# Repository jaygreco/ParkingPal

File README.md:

# ParkingPal
An open-source distance meter for easy garage parking. See [the thingiverse page](https://www.thingiverse.com/thing:3448336) for more info.

## How to use
Compile for the Arduino Pro Micro and upload. By default, the firmware is built for 8 LEDs (the NeoPixel Stick), and will poll the sensor at 3Hz until the read distance has been stable for roughly 10 seconds.

Single-pressing the button will change the operating mode. Double-clicking will cycle the brightness, and long-pressing will set the default parking distance. To set the default parking distance properly, park the car at the normal parking distance, and then long-press the button while making sure to stay clear of the ultrasonic sensor. Once set, the buzzer will beep once.

There are some configuration options in `config.h`. They should be pretty self-explanatory. There really isn't much need to change these unless you want to tweak some specific behavior. 

## Parts list
There's a more detailed BOM [here](https://github.com/jaygreco/ParkingPal/blob/master/PCB/0.1/MCU/MCU_BOM.xlsx).
### Required
| Qty | Part              | Link                                                                |
|-----|-------------------|---------------------------------------------------------------------|
| 1   | Arduino Pro Micro | [SparkFun](https://www.sparkfun.com/products/12640)                 |
| 1   | NeoPixel Stick    | [SparkFun](https://www.sparkfun.com/products/12661)                 |
| 1   | HC-SR04 Sensor    | [SparkFun](https://www.sparkfun.com/products/13959)                 |
| 1   | SMT Pushbutton    | [SparkFun](https://www.sparkfun.com/products/8720)                  |
| 1   | USB A Connector   | [Digikey](https://www.digikey.com/products/en?keywords=380-1412-ND) |
| 1   | PCB - MCU         | [OSHPark](https://oshpark.com/shared_projects/L5AVMKPm)             |
| 1   | PCB - SMU         | [OSHPark](https://oshpark.com/shared_projects/UerOD9Ji)             |

### Optional (to include buzzer)
| Qty | Part            | Link                                                                        |
|-----|-----------------|-----------------------------------------------------------------------------|
| 1   | 12mm Buzzer     | [SparkFun](https://www.sparkfun.com/products/7950)                          |
| 1   | 10k Resistor    | [Digikey](https://www.digikey.com/products/en?keywords=RMCF0201FT10K0CT-ND) |
| 1   | 2N7002 N-Ch Fet | [Digikey](https://www.digikey.com/products/en?keywords=2N7002-TPMSCT-ND)    |

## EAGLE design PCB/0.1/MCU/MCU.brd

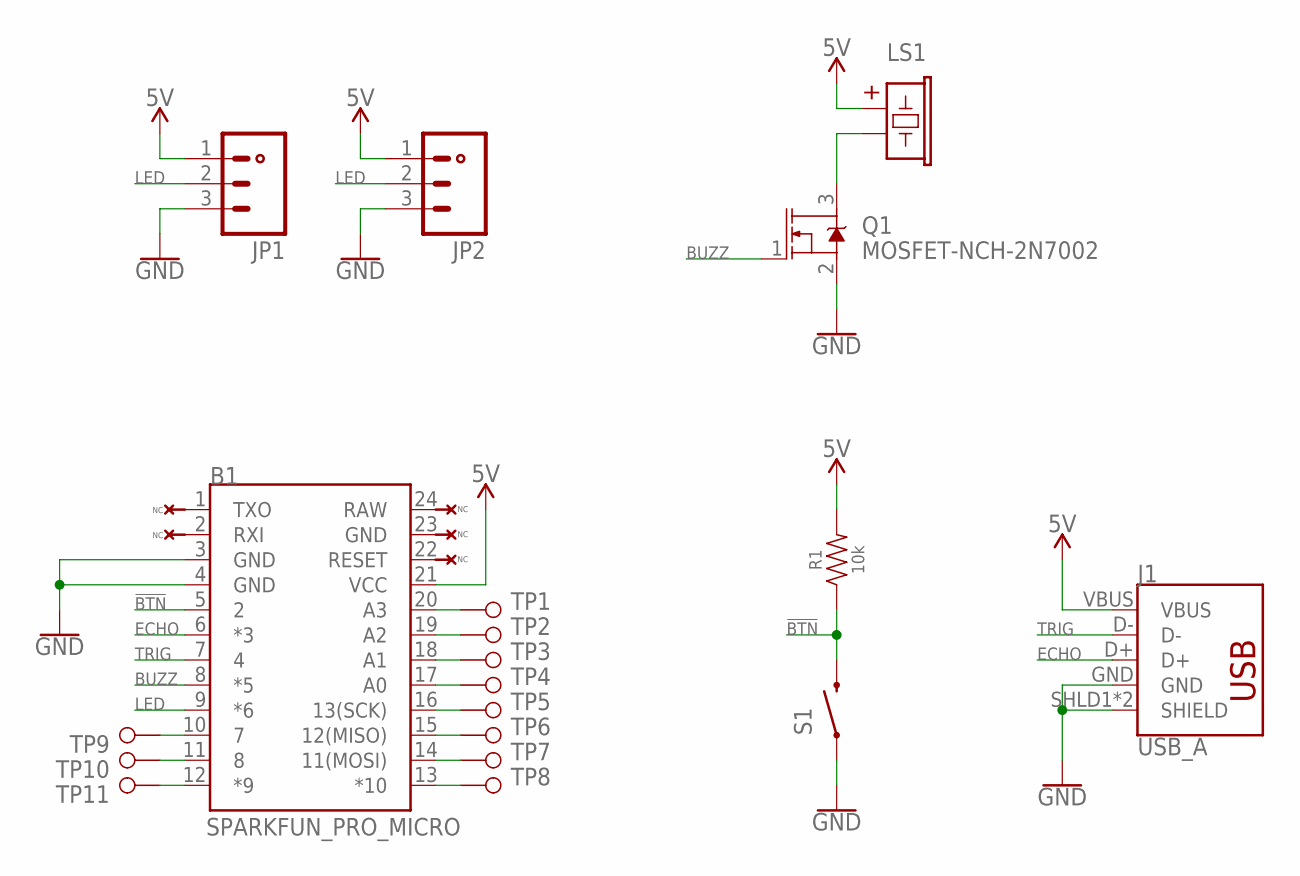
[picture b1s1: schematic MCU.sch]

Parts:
B1: SPARKFUN_PRO_MICRO
J1: USB_A; USB-A-H
JP1, JP2: M03PTH; 1X03
LS1: BUZZER-PTH_KIT; BUZZER-12MM-KIT
Q1: MOSFET-NCH-2N7002; SOT23-3
R1: 10k; 0603
S1: SWITCH-MOMENTARY-2SMD-REDUNDANT; TACTILE-SWITCH-SMD
TP1, TP2, TP3, TP4, TP5, TP6, TP7, TP8, TP9, TP10, TP11: TEST-POINT3X5; PAD.03X.05

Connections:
5V: B1.21 (VCC), J1.VBUS, JP1.1, JP2.1, LS1.+ (1), R1.2
!BTN: B1.5 (2), R1.1, S1.3 (2), S1.4 (2)
BUZZ: B1.8 (*5), Q1.1 (G)
ECHO: B1.6 (*3), J1.D+
GND: B1.3 (GND), B1.4 (GND), B1.23 (GND), J1.GND, J1.SHLD1 (SHIELD), J1.SHLD2 (SHIELD), JP1.3, JP2.3, Q1.2 (S), S1.1, S1.2 (1)
LED: B1.9 (*6), JP1.2, JP2.2
unnamed: B1.16 (13(SCK)), TP5.P$1
unnamed: B1.15 (12(MISO)), TP6.P$1
unnamed: B1.14 (11(MOSI)), TP7.P$1
unnamed: LS1.- (2), Q1.3 (D)
unnamed: B1.13 (*10), TP8.P$1
unnamed: B1.20 (A3), TP1.P$1
unnamed: B1.19 (A2), TP2.P$1
unnamed: B1.18 (A1), TP3.P$1
unnamed: B1.17 (A0), TP4.P$1
unnamed: B1.10 (7), TP9.P$1
unnamed: B1.11 (8), TP10.P$1
unnamed: B1.12 (*9), TP11.P$1
RAW: B1.24 (RAW)
TRIG: B1.7 (4), J1.D-

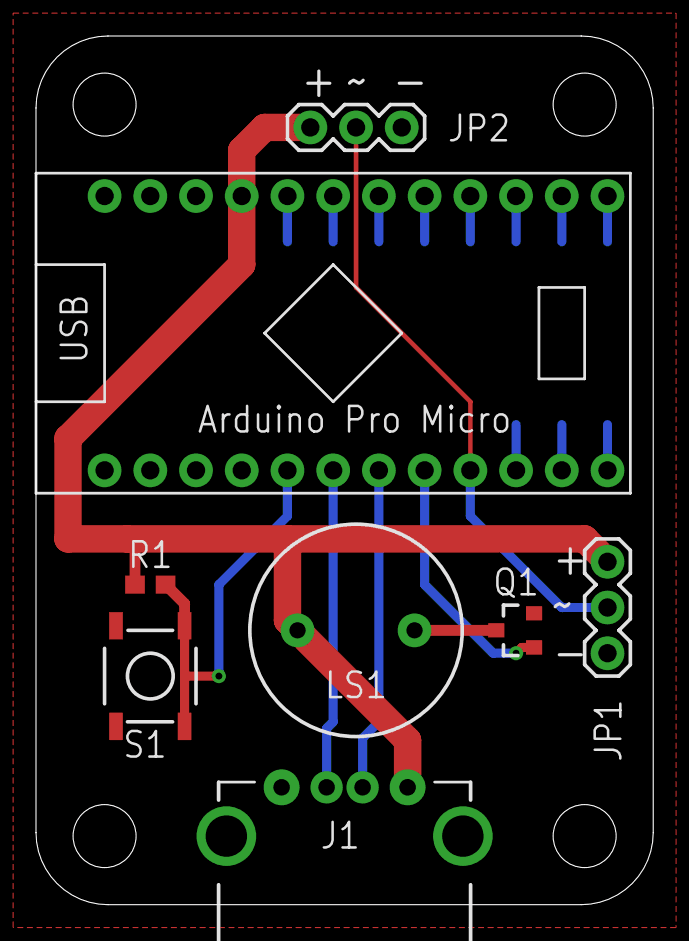
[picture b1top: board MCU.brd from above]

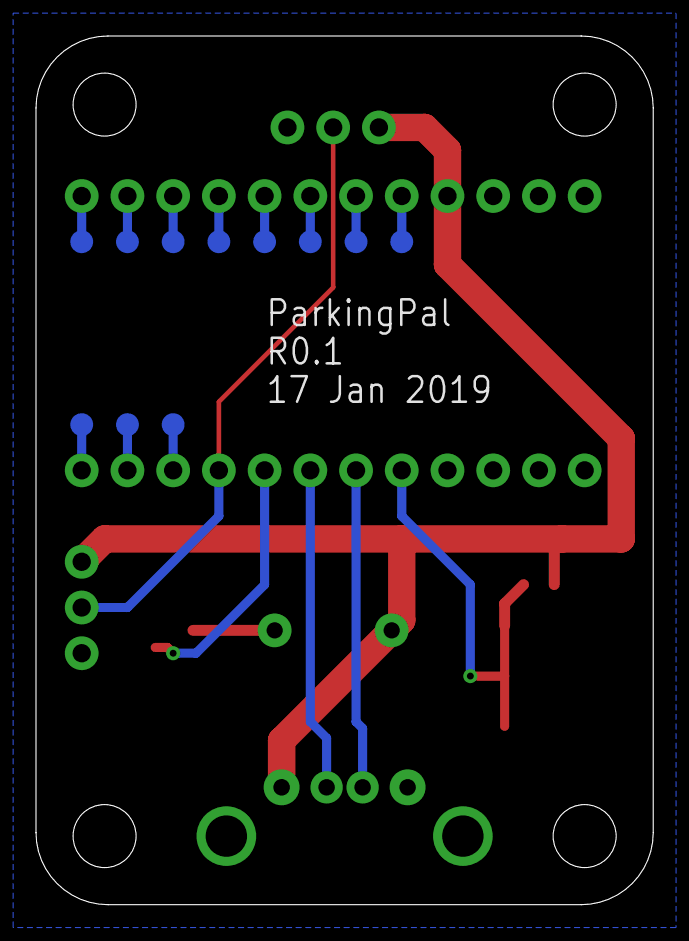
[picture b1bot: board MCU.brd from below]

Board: 2 copper layers, 34.3 x 48.3 mm, 19 parts (11 on the bottom side), 19 nets.

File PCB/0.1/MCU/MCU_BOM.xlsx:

Qty | Value | Part | Distributor | Package | Parts | Description
1 | 10k | RMCF0201FT10K0CT-ND | Digikey | 0603 | R1 | 0603 Resistor
1 | BUZZER-PTH_KIT | COM-07950 | Sparkfun | BUZZER-12MM-KIT | LS1 | 12mm Buzzer
1 | MOSFET-NCH-2N7002 | 2N7002-TPMSCT-ND | Digikey | SOT23-3 | Q1 | N-channel MOSFET
1 | SPARKFUN_PRO_MICRO_5V | DEV-12640 | Sparkfun | SPARKFUN_PRO_MICRO | B1 | SparkFun Pro Micro
1 | SWITCH-MOMENTARY-2SMD-REDUNDANT | COM-08720 | Sparkfun | TACTILE-SWITCH-SMD | S1 | NO SMT Button
1 | USB_A | 380-1412-ND | Digikey | USB-A-H | J1 | USB-A Connector

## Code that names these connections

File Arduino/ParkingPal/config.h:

// ParkingPal defines and macros.

#ifndef CONFIG_H
#define CONFIG_H

// Hardware configuration
#define BTN_PIN 2
#define ECHO_PIN 3
#define TRIG_PIN 4
#define BUZZ_PIN 5
#define LED_PIN 6

// Beep configuration
#define BEEP_PERIOD_MS 500  // How long to beep for
#define BEEP_FREQ 2048      // Frequency to beep at
#define BEEP_DUTY_ON 50     // Buzzer duty cycle when on (percent)
#define BEEP_DUTY_OFF 0     // Buzzer duty cycle when off
#define BEEP_DUTY_SFX 10    // Duty cycle for sound effects (percent)

//Sensor configuration
#define PING_TIMEOUT 25000      // Sets maximum sensor distance
#define WINDOW_FILTER_TIME_S 10 // Window filter length in seconds
#define POLL_FREQ 3             // How frequently to poll the sensor
#define POLL_T_MS (1.0/POLL_FREQ)*1000
#define NUM_SEN_SAMPLES POLL_FREQ * WINDOW_FILTER_TIME_S
#define NUM_DIST_SAMPLES 3      // Distance window filter 

// LED configuration
#define FLIP_LEDS true		// Flip LED orientation
#define NUM_LEDS 8          // Number of LEDs in your light setup
#define MAX_LED_MODES 4     // Number of LED modes to switch through
#define BRIGHTNESS_MIN 50   // Lowest brightness setting
#define BRIGHTNESS_MAX 250  // Maximum allowable brightness of LEDs
#define BRIGHTNESS_INC 50   // Amount to increment brightness by
#define LED_FADE_MS 3000    // How long to fade out LEDs when going idle

// LED modes
#define LED_MODE_BAR 0
#define LED_MODE_RG 1
#define LED_MODE_RYG 2
#define LED_MODE_STOPLIGHT 3
#define LED_FLASH_WAVE 0
#define LED_FLASH_BLUE 1
#define LED_FLASH_STARTUP 2
#define LED_FLASH_MODE 3

// System configuration
#define DIST_THRESHOLD_CM 5     // Don't wake unless distance has changed this much
#define DISTANCE_MAX_CM 350     // Maximum distance to measure
#define SAFE_ZONE_CM 20         // Safe zone buffer ahead of beeping
#define LOOP_DELAY 50           // How frequently to poll the loop
#define USE_DEEP_SLEEP false     // Sleep using low power library

// Debug settings
//#define DEBUG
#define PARAM_LOGGING
#define LED_LOGGING
#define LOOP_LOGGING
#define EEPROM_LOGGING
#define PING_LOGGING
#define BUTTON_LOGGING

#endif

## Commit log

2019-03-28 Remove duplicate files
